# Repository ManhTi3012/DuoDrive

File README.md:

# ⚠️ **WARNING: PROJECT UNDER DEVELOPMENT, CHANGES WILL BE MADE**

# DuoDrive
DuoDrive is a closed-loop brushed motor driver design to offer simple and affordable open-source hardware and software:
* Running internal PID loop for driving up to 2 brushed motor.
* Increment-type and absolute-type encoder (not yet).
* UART interface and CAN Bus (no firmware support yet).
* Velocity and position control.

You can also use SimpleFOC library to control a single BLDC motor.

<!---  An autonomous robot using DuoDrive's velocity control can still run straight without line or gyro correction.
   --->

For configuring the driver, checkout the [Web Tool](https://manhti3012.github.io/DuoDriveConfigTool/)

# Hardware
DuoDrive is designed to handle high current within a small footprint:
* Voltage input: 12-24v, 30V absolute maximum
* Maximum continuous current: 25A
* Power traces are exposed for high current handling, beware of shorts
* Dimensions: 49mm x 75mm

Step file can be found in "3D" folder.
# Firmware
The firmware is expected to be stable for now, but further testing still needed for stability-related bugs.
Please open a new issues if you encounter any problem.
For detailed explanation and methods, check Wiki page.

# Documentation
For more detail, check the [WIKI Page](https://github.com/ManhTi3012/DuoDrive/wiki)

# Liability
* The software and hardware are still in development and may contain bugs, errors, or incomplete features.
* Users are encouraged to use this software and hardware responsibly and at their own risk.

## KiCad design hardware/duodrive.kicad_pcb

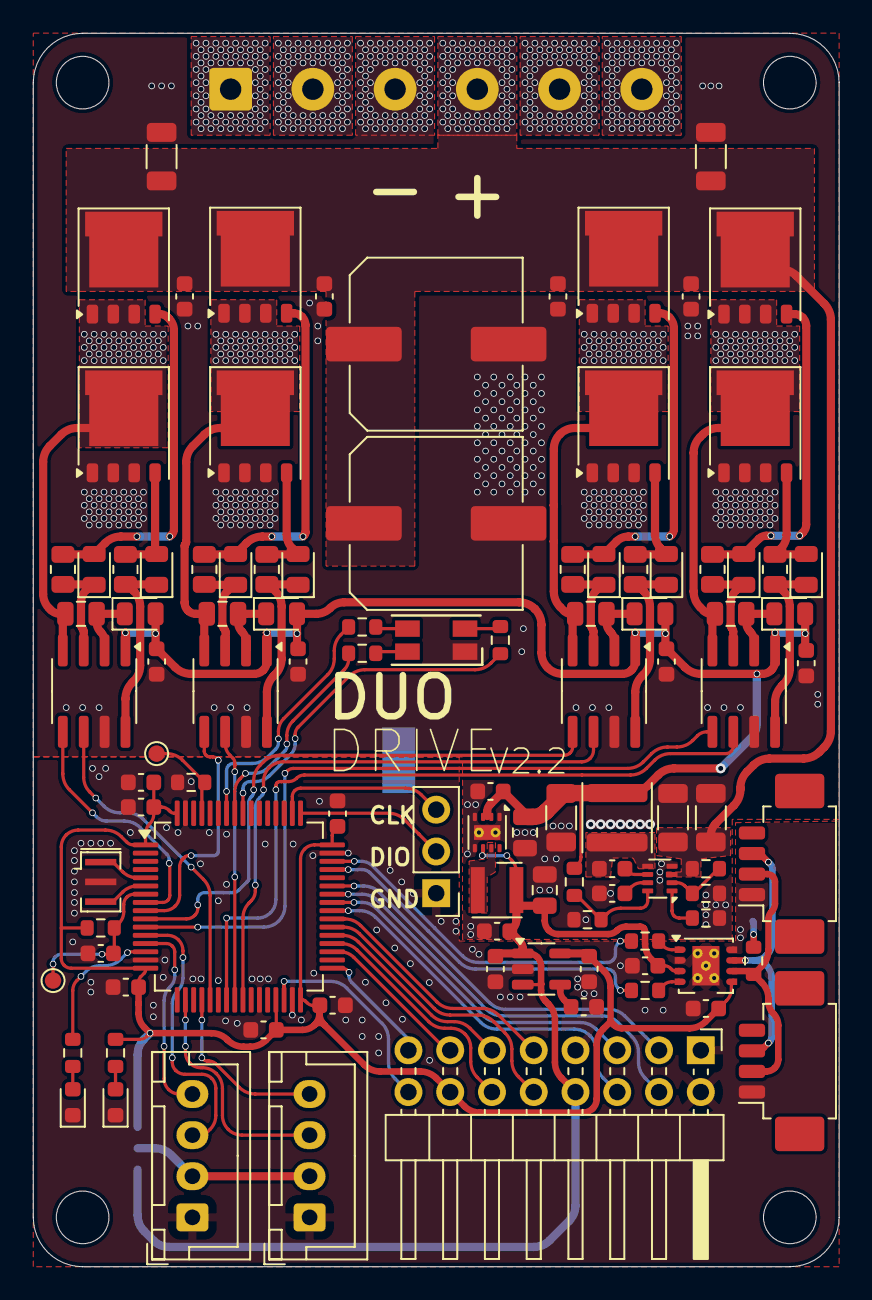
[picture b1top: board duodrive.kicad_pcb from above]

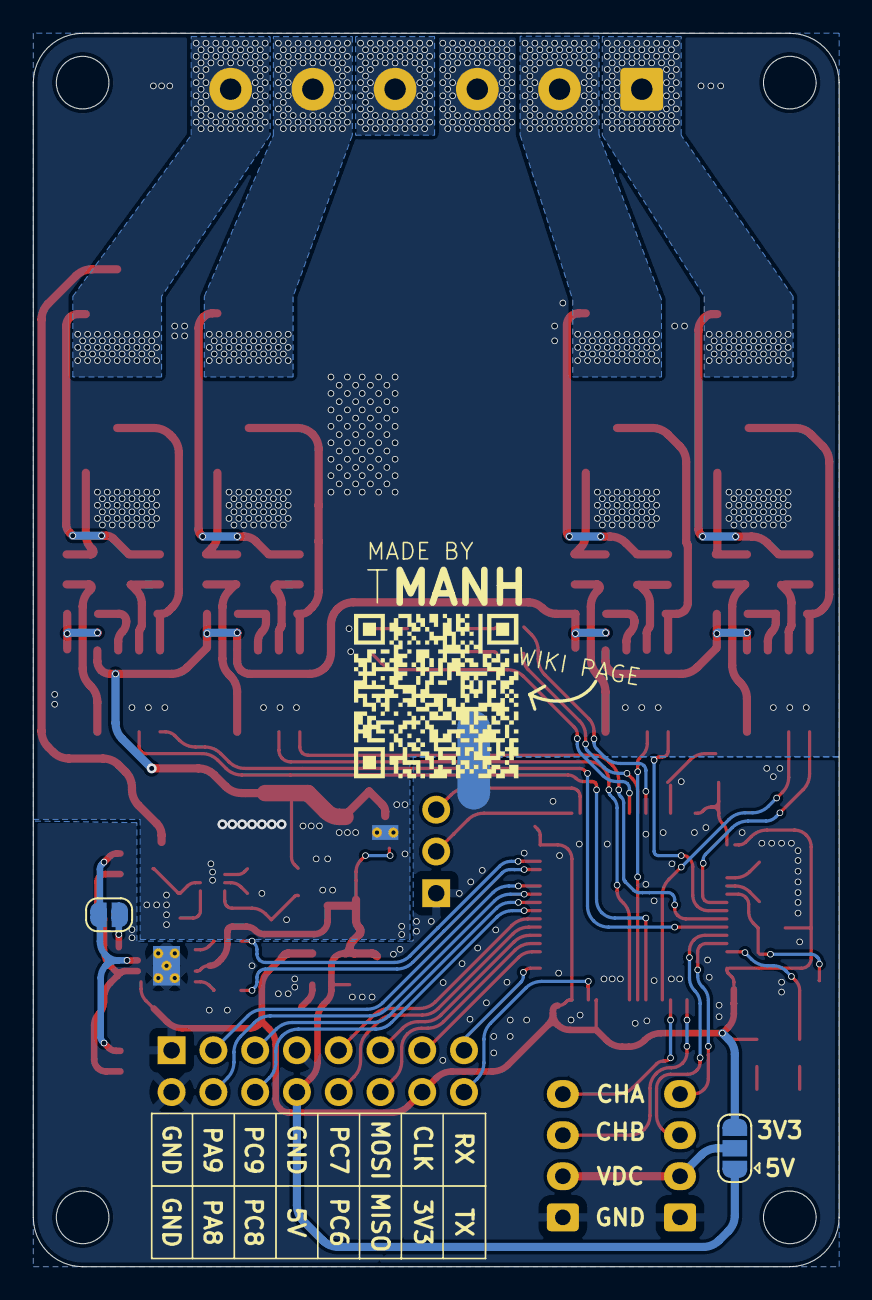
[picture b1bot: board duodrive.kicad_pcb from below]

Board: 2 copper layers, 49.0 x 75.0 mm, 111 parts (3 on the bottom side), 84 nets.

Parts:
C1, C3: 470uF; C_Elec_10x10.2
C2, C4, C5, C6, C8, C11, C13, C15, C16, C19, C21, C22, C25, C30, C36, C41, C42: 100nF; C_0603_1608Metric
C7, C9, C14, C17: 1uF; C_0805_2012Metric
C10, C12: 10uF; C_0603_1608Metric
C18, C20, C27: 10uF; C_1206_3216Metric
C23, C24: 22uF; C_1206_3216Metric
C26: 470pF; C_0603_1608Metric
C29, C31: 22uF; C_0805_2012Metric
C32, C33, C34, C35: 1uF; C_0603_1608Metric
D1, D20: LED_Small; LED_0603_1608Metric
D4: LED_KRGB; LED_RGB_1210
D6, D7, D8, D9, D10, D11, D12, D13, D14, D15, D16, D17: B5819WS; D_0805_2012Metric
H1, H2, H3, H4: MountingHole_Pad; MountingHole_3.2mm_M3
J2: Conn_02x08_Odd_Even; PinHeader_2x08_P2.54mm_Horizontal
J3: SWD; PinHeader_1x03_P2.54mm_Vertical
J4: CAN_IN; Molex_PicoBlade_53261-0471_1x04-1MP_P1.25mm_Horizontal
J5: CAN_OUT; Molex_PicoBlade_53261-0471_1x04-1MP_P1.25mm_Horizontal
J6: POWER; TerminalBlock_MetzConnect_Type094_RT03506HBLU_1x06_P5.00mm_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
J7: ENCODER1; JST_XH_B4B-XH-A_1x04_P2.50mm_Vertical
J8: ENCODER2; JST_XH_B4B-XH-A_1x04_P2.50mm_Vertical
JP1: Jumper_2_Open; SolderJumper-2_P1.3mm_Open_RoundedPad1.0x1.5mm
JP2: Jumper_3_Open; SolderJumper-3_P1.3mm_Open_RoundedPad1.0x1.5mm
L1: 12uH; L_APV_ANR4020
L2: 2.2uH; L_Wurth_WE-LQSH-3012
NT1: NetTie_2; NetTie-2_SMD_Pad2.0mm
Q1, Q2, Q3, Q4, Q5, Q7: DON50N04; PQFN-8-EP_6x5mm_P1.27mm_Generic
Q6, Q8: NMOS-8PINS; PQFN-8-EP_6x5mm_P1.27mm_Generic
R1, R3, R8, R9, R10, R11: 1K; R_0603_1608Metric
R2, R5, R6: 10K; R_0603_1608Metric
R4: 115K; R_0603_1608Metric
R7: 470K; R_0603_1608Metric
R12: 56K; R_0603_1608Metric
R13, R14, R15, R16, R17, R18, R19, R20: 10R; R_0805_2012Metric
R21, R22: 47R; R_0603_1608Metric
R23: 120R; R_0603_1608Metric
TP1, TP2: TestPoint; TestPoint_Pad_D1.0mm
U1: TCAN1044V; Texas_S-PVSON-N8_ThermalVias
U2, U5, U6, U7: UCC27211; SOIC-8_3.9x4.9mm_P1.27mm
U3: TPS62173DSG; WSON-8-1EP_2x2mm_P0.5mm_EP0.9x1.6mm_ThermalVias
U4: STM32G431RBTx; LQFP-64_10x10mm_P0.5mm
U8: TPS62933; SOT-583-8
U10: MIC5219-3.3YM5; SOT-23-5
Y1: Resonator; Resonator_SMD_Murata_CSTxExxV-3Pin_3.0x1.1mm

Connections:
+3.3V: C2.1, C4.1, C8.1, C11.1, C12.1, C21.1, C22.1, C36.1, J2.14, JP2.3 (B), R5.2, R8.1, U1.5 (VIO), U4.1 (VBAT), U4.16 (VDD), U4.29 (VDDA), U4.32 (VDD), U4.48 (VDD), U4.64 (VDD), U10.5 (OUT)
+5V: C10.1, C13.1, C31.1, C42.1, J2.8, JP2.1 (A), L2.2, U1.3 (VCC), U3.6 (VOS), U10.1 (IN), U10.3 (EN)
+10V: C15.1, C16.1, C19.1, C20.2, C29.1, C30.1, C41.1, D8.2 (A), D9.2 (A), D12.2 (A), D17.2 (A), L1.2, R4.2, U2.1 (VCC), U3.2 (VIN), U3.3 (EN), U5.1 (VCC), U6.1 (VCC), U7.1 (VCC)
BOOT: R2.2, TP1.1, U4.61 (PB8)
CANRX: R21.1, U4.45 (PA11)
CANTX: R22.1, U4.46 (PA12)
CAN_H: J4.3, J5.3, JP1.1 (A), U1.7 (CANH)
CAN_L: J4.2, J5.2, R23.2, U1.6 (CANL)
GND: C1.2, C3.2, C15.2, C16.2, C18.1, C19.2, C20.1, C23.1, C24.1, C25.1, C27.1, C29.2, C30.2, C31.2, C32.2, C33.2, C34.2, C35.2, C41.2, C42.2, D4.1 (K), J6.3, NT1.2, Q2.1 (S), Q2.2 (S), Q2.3 (S), Q4.1 (S), Q4.2 (S), Q4.3 (S), Q6.1 (S), Q6.2 (S), Q6.3 (S), Q8.1 (S), Q8.2 (S), Q8.3 (S), R6.1, R11.1, R12.2, U2.7 (COM), U3.1 (PGND), U3.4 (AGND), U3.5 (FB), U3.9 (PAD), U5.7 (COM), U6.7 (COM), U7.7 (COM), U8.4 (GND)
GNDS: C2.2, C4.2, C5.1, C8.2, C10.2, C11.2, C12.2, C13.2, C21.2, C22.2, C26.2, C36.2, D1.1 (K), D20.1 (K), J2.1, J2.2, J2.7, J3.1, J4.1, J5.1, J7.1, J8.1, NT1.1, R2.1, U1.2 (GND), U1.8 (STB), U1.9 (THERMAL), U4.15 (VSS), U4.27 (VSSA), U4.31 (VSS), U4.47 (VSS), U4.63 (VSS), U10.2 (GND), Y1.2
H1: U2.5 (HIN), U4.8 (PC0)
H2: U4.9 (PC1), U5.5 (HIN)
H3: U4.10 (PC2), U6.5 (HIN)
H4: U4.11 (PC3), U7.5 (HIN)
L1: U2.6 (LIN), U4.21 (PA7)
L2: U4.24 (PB0), U5.6 (LIN)
L3: U4.25 (PB1), U6.6 (LIN)
L4: U4.23 (PC5), U7.6 (LIN)
LED1: R1.1, U4.14 (PA2)
LED2: R9.1, U4.58 (PB5)
LED3: R10.1, U4.57 (PB4)
LED4: R3.1, U4.56 (PB3)
MOTOR_OUT_1: C7.2, J6.1, Q1.1 (S), Q1.2 (S), Q1.3 (S), Q2.5 (D), U2.4 (VS)
MOTOR_OUT_2: C9.2, J6.2, Q3.1 (S), Q3.2 (S), Q3.3 (S), Q4.5 (D), U5.4 (VS)
MOTOR_OUT_3: C17.2, J6.5, Q5.1 (S), Q5.2 (S), Q5.3 (S), Q6.5 (D), U6.4 (VS)
MOTOR_OUT_4: C14.2, J6.6, Q7.1 (S), Q7.2 (S), Q7.3 (S), Q8.5 (D), U7.4 (VS)
unnamed: D1.2 (A), R1.2
unnamed: D4.4 (BA), R10.2
unnamed: D4.3 (GA), R9.2
unnamed: D4.2 (RA), R3.2
unnamed: D6.2 (A), Q1.4 (G), R13.1
unnamed: D6.1 (K), R13.2, U2.3 (HO)
unnamed: D7.2 (A), Q2.4 (G), R14.1
unnamed: D7.1 (K), R14.2, U2.8 (LO)
unnamed: C7.1, D8.1 (K), U2.2 (VB)
unnamed: C9.1, D9.1 (K), U5.2 (VB)
unnamed: D10.2 (A), Q3.4 (G), R15.1
unnamed: D10.1 (K), R15.2, U5.3 (HO)
unnamed: D11.2 (A), Q4.4 (G), R16.1
unnamed: D11.1 (K), R16.2, U5.8 (LO)
unnamed: C17.1, D12.1 (K), U6.2 (VB)
unnamed: D13.2 (A), Q5.4 (G), R17.1
unnamed: D13.1 (K), R17.2, U6.3 (HO)
unnamed: D14.2 (A), Q6.4 (G), R18.1
unnamed: D14.1 (K), R18.2, U6.8 (LO)
unnamed: D15.2 (A), Q7.4 (G), R19.1
unnamed: D15.1 (K), R19.2, U7.3 (HO)
unnamed: D16.2 (A), Q8.4 (G), R20.1
unnamed: D16.1 (K), R20.2, U7.8 (LO)
unnamed: C14.1, D17.1 (K), U7.2 (VB)
unnamed: D20.2 (A), R8.2
unnamed: JP1.2 (B), R23.1
unnamed: R21.2, U1.4 (RXD)
unnamed: R22.2, U1.1 (TXD)
unnamed: L2.1, U3.7 (SW)
unnamed: U4.5 (PF0), Y1.1
unnamed: U4.6 (PF1), Y1.3
unnamed: C6.2, U8.6 (BST)
unnamed: R7.1, R12.1, U8.2 (EN)
unnamed: R4.1, R6.2, U8.8 (FB)
unnamed: R11.2, U8.1 (RT)
unnamed: C25.2, U8.7 (SS)
unnamed: C6.1, L1.1, U8.5 (SW)
unnamed: C26.1, U10.4 (BP)
PA8: J2.4, U4.42 (PA8)
PA9: J2.3, U4.43 (PA9)
PC6: J2.10, U4.38 (PC6)
PC7: J2.9, U4.39 (PC7)
PC8: J2.6, U4.40 (PC8)
PC9: J2.5, U4.41 (PC9)
PWM1A: J7.3, U4.12 (PA0)
PWM1B: J7.4, U4.13 (PA1)
PWM2A: J8.3, U4.18 (PA4)
PWM2B: J8.4, U4.20 (PA6)
RX: J2.15, U4.33 (PB11)
Reset: C5.2, R5.1, TP2.1, U4.7 (PG10)
SPI_CLK: J2.13, U4.35 (PB13)
SPI_MISO: J2.12, U4.36 (PB14)
SPI_MOSI: J2.11, U4.37 (PB15)
SWCLK: J3.3, U4.50 (PA14)
SWDIO: J3.2, U4.49 (PA13)
TX: J2.16, U4.30 (PB10)
VBUS: J7.2, J8.2, JP2.2 (C)
VDC: C1.1, C3.1, C18.2, C23.2, C24.2, C27.2, C32.1, C33.1, C34.1, C35.1, J6.4, Q1.5 (D), Q3.5 (D), Q5.5 (D), Q7.5 (D), R7.2, U8.3 (VIN)

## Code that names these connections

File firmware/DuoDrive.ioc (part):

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Mcu.Name=STM32G431R(6-8-B)Tx
Mcu.Package=LQFP64
Mcu.UserName=STM32G431RBTx
PA0.Signal=S_TIM2_CH1
PA1.Signal=S_TIM2_CH2
PA11.GPIOParameters=GPIO_PuPd
PA11.GPIO_PuPd=GPIO_PULLUP
PA11.Mode=FDCAN_Activate
PA11.Signal=FDCAN1_RX
PA12.Mode=FDCAN_Activate
PA12.Signal=FDCAN1_TX
PA13.Mode=Serial_Wire
PA13.Signal=SYS_JTMS-SWDIO
PA14.Mode=Serial_Wire
PA14.Signal=SYS_JTCK-SWCLK
PA4.Signal=S_TIM3_CH2
PA6.Signal=S_TIM3_CH1
PA7.Mode=PWM Generation1 CH1 CH1N
PA7.Signal=TIM1_CH1N
PB0.Mode=PWM Generation2 CH2 CH2N
PB0.Signal=TIM1_CH2N
PB1.Mode=PWM Generation3 CH3 CH3N
PB1.Signal=TIM1_CH3N
PB10.Mode=Asynchronous
PB10.Signal=USART3_TX
PB11.Mode=Asynchronous
PB11.Signal=USART3_RX
PB13.Mode=Full_Duplex_Master
PB13.Signal=SPI2_SCK
PB14.Mode=Full_Duplex_Master
PB14.Signal=SPI2_MISO
PB15.Mode=Full_Duplex_Master
PB15.Signal=SPI2_MOSI
PB3.Signal=GPIO_Output
PB4.Signal=GPIO_Output
PB5.Signal=GPIO_Output
PB6.Signal=GPIO_Output
PB8-BOOT0.Signal=GPIO_Input
PC0.Signal=S_TIM1_CH1
PC1.Signal=S_TIM1_CH2
PC2.Signal=S_TIM1_CH3
PC3.Signal=S_TIM1_CH4
PC5.Mode=PWM Generation4 CH4 CH4N
PC5.Signal=TIM1_CH4N
PC8.Mode=I2C
PC8.Signal=I2C3_SCL
PC9.Mode=I2C
PC9.Signal=I2C3_SDA
PF0-OSC_IN.Mode=HSE-External-Oscillator
PF0-OSC_IN.Signal=RCC_OSC_IN
PF1-OSC_OUT.Mode=HSE-External-Oscillator
PF1-OSC_OUT.Signal=RCC_OSC_OUT
RCC.HSE_VALUE=8000000
RCC.SYSCLKFreq_VALUE=160000000
RCC.SYSCLKSource=RCC_SYSCLKSOURCE_PLLCLK
board=custom

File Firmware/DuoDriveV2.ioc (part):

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Mcu.Name=STM32G431R(6-8-B)Tx
Mcu.Package=LQFP64
Mcu.UserName=STM32G431RBTx
PA0.Signal=S_TIM2_CH1
PA1.Signal=S_TIM2_CH2
PA11.Mode=FDCAN_Activate
PA11.Signal=FDCAN1_RX
PA12.Mode=FDCAN_Activate
PA12.Signal=FDCAN1_TX
PA13.Mode=Serial_Wire
PA13.Signal=SYS_JTMS-SWDIO
PA14.Mode=Serial_Wire
PA14.Signal=SYS_JTCK-SWCLK
PA4.Signal=S_TIM3_CH2
PA6.Signal=S_TIM3_CH1
PA7.Mode=PWM Generation1 CH1 CH1N
PA7.Signal=TIM1_CH1N
PA8.Signal=S_TIM1_CH1
PA9.Signal=S_TIM1_CH2
PB0.Mode=PWM Generation2 CH2 CH2N
PB0.Signal=TIM1_CH2N
PB1.Mode=PWM Generation3 CH3 CH3N
PB1.Signal=TIM1_CH3N
PB10.Mode=Asynchronous
PB10.Signal=USART3_TX
PB11.Mode=Asynchronous
PB11.Signal=USART3_RX
PB12.Signal=GPIO_Input
PB3.Signal=GPIO_Output
PB4.Signal=GPIO_Output
PB5.Signal=GPIO_Output
PB6.Signal=GPIO_Output
PB8-BOOT0.Signal=GPIO_Input
PC2.Signal=S_TIM1_CH3
PC3.Signal=S_TIM1_CH4
PC5.Mode=PWM Generation4 CH4 CH4N
PC5.Signal=TIM1_CH4N
PF0-OSC_IN.Mode=HSE-External-Oscillator
PF0-OSC_IN.Signal=RCC_OSC_IN
PF1-OSC_OUT.Mode=HSE-External-Oscillator
PF1-OSC_OUT.Signal=RCC_OSC_OUT
RCC.HSE_VALUE=8000000
RCC.SYSCLKFreq_VALUE=160000000
RCC.SYSCLKSource=RCC_SYSCLKSOURCE_PLLCLK
board=custom

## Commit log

2025-04-22 Create temp
2025-04-28 Rename Screenshot_49.png to Kicad.png
2025-07-15 update and clean up
    clean up the tree and update 100+ files
2025-07-15 reupload files
2025-07-16 more uart commands and functions
2025-07-18 fix uart command
2025-07-24 Update Command and parsing
    fix and update all parse command, prepare machine command for a more efficient communication than human version
2025-07-24 UART parser update
    Added machine communication and fix print function
2025-07-25 minor bug fix
2025-07-25 Hardware bug fix
    Fixed buck converter output bulk capacitor not connected to ground
    Added pull up resistor at buck EN pin instead of connect it to VCC
2025-08-01 Remake Motor Control
    Add more config-able parameter, new Timer Interrupt-Based PID Clock
2025-08-05 Minor bug fix and QOL feature
    Minor bug fix:
    - Changed layout of buck converter for bigger capacitor and added pull up resistor
    - Fixed buck output capacitor connected to wrong pin
    - Changed passive component value to match final product value
    QOL Feature:
    - Added QR code on the bottom silkscreen for wiki page
2025-08-07 Bug fixes and new feature
    - Fix UART not able to receive constant data stream
    - Fix velocity calculation that result in wrong result
    - Now config can be saved in internal flash
    - All config are now able to change through UART command
    - New async PID loop, can be set between 1Hz and 10kHz
2025-09-15 QOL Fix
    - Encoder PPR overflow fix
    - Changed uart parser method to DMA circular buffer from single char processing.
2025-09-15 added images
2025-09-16 clean up
2025-09-23 Final Clean Up
2025-10-04 NEW Version
2025-10-09 test
2025-10-10 layout
2025-10-11 layout update
2025-10-13 finish and polishing
2025-10-17 polishing
2025-11-02 PCB Upload
2025-11-09 layout and component changes
